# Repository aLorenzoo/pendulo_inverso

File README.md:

# pendulo_inverso
Pendulo-Inverso
En este txt iré describiendo alguno de los pasos y procesos que iré siguiendo con el objetivo de crear un pendulo inverso. PLANNING:

1. Buscar referencias
2. Encontrar huellas de los elementos requeridos
3. Montar las huellas que sean necesarias
4. Juntarlas todas en una sola PCB
5. Llevarla a Enrique para comprobar que funciona correctamente, y si no es así, corregir los errores
6. Una vez comprobado que la PCB funciona a la perfección, encargar su fabricación por Internet https://www.pcbway.es/?currency=3
7. Conseguir los motores y las ruedas https://www.amazon.es/Gebildet-Motorreductor-Tracción-Robótico-Neumático/dp/B08D39MFN1/ref=asc_df_B08D39MFN1/?tag=&linkCode=df0&hvadid=420349540689&hvpos=&hvnetw=g&hvrand=10269854428416406848&hvpone=&hvptwo=&hvqmt=&hvdev=c&hvdvcmdl=&hvlocint=&hvlocphy=1005480&hvtargid=pla-937905506568&mcid=4c17839e2fe332fd8fbfa763e271e5d1&ref=&adgrpid=94419898965&th=1
8. Diseñar una carcasa en 3D e imprimirla en la politécnica
9. Montar y soldar todo
10. Comprobar su funcionamiento y que cumple los requisitos pedidos en la práctica
11. Pulir detalles

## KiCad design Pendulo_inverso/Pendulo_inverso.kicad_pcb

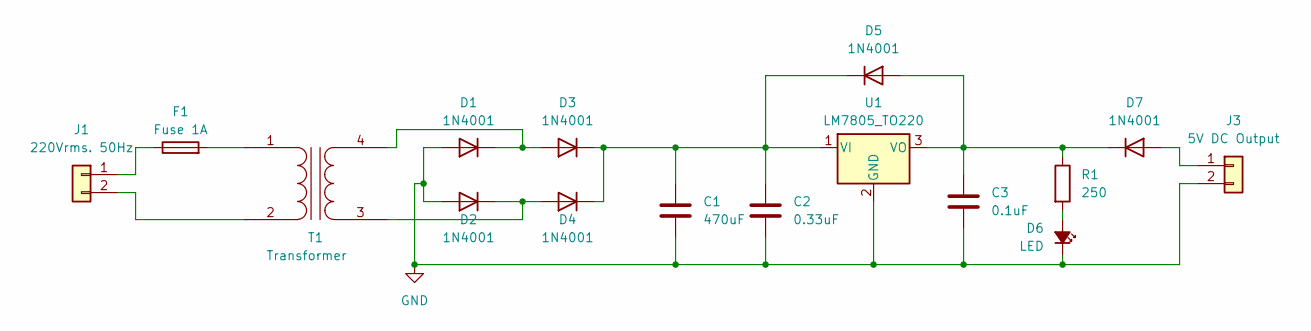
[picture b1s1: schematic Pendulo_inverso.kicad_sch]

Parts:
C1: 470uF; CP_Elec_3x5.3
C2: 0.33uF; CP_Elec_3x5.3
C3: 0.1uF; CP_Elec_3x5.3
D1, D2, D3, D4, D5, D7: 1N4001; D_DO-41_SOD81_P10.16mm_Horizontal
D6: LED; LED_0201_0603Metric
F1: Fuse 1A; R_0201_0603Metric
J1: 220Vrms. 50Hz; Banana_Jack_2Pin
J3: 5V DC Output; Banana_Jack_2Pin
R1: 250; R_0201_0603Metric
T1: Transformer; Transformer_Toroid_Horizontal_D18.0mm
U1: LM7805_TO220; TO-220-3_Vertical

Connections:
GND: C1.2, C2.2, C3.2, D1.2 (A), D2.2 (A), D6.1 (K), U1.2 (GND); also elsewhere on the board
unnamed: D1.1 (K), D3.2 (A), T1.4 (SB)
unnamed: D2.1 (K), D4.2 (A), T1.3 (SA)
unnamed: C1.1, C2.1, D3.1 (K), D4.1 (K), D5.1 (K), U1.1 (VI)
unnamed: C3.1, D5.2 (A), D7.1 (K), R1.1, U1.3 (VO)
unnamed: D6.2 (A), R1.2
unnamed 6: D7.2 (A); also elsewhere on the board
unnamed: F1.1, J1.1
unnamed: J1.2, T1.2 (AB)
unnamed: F1.2, T1.1 (AA)

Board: 2 copper layers, 16 parts (0 on the bottom side), 10 nets, no tracks yet.

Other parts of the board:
J2: 5V DC Output; Banana_Jack_2Pin

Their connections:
GND: J2.2; also elsewhere on the board
unnamed 6: J2.1; also elsewhere on the board

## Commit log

2024-03-16 Create Preguntas
